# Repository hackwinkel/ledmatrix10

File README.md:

# ledmatrix10
10x10 RGB led display using "dumb" leds and an ESP32 to drive them

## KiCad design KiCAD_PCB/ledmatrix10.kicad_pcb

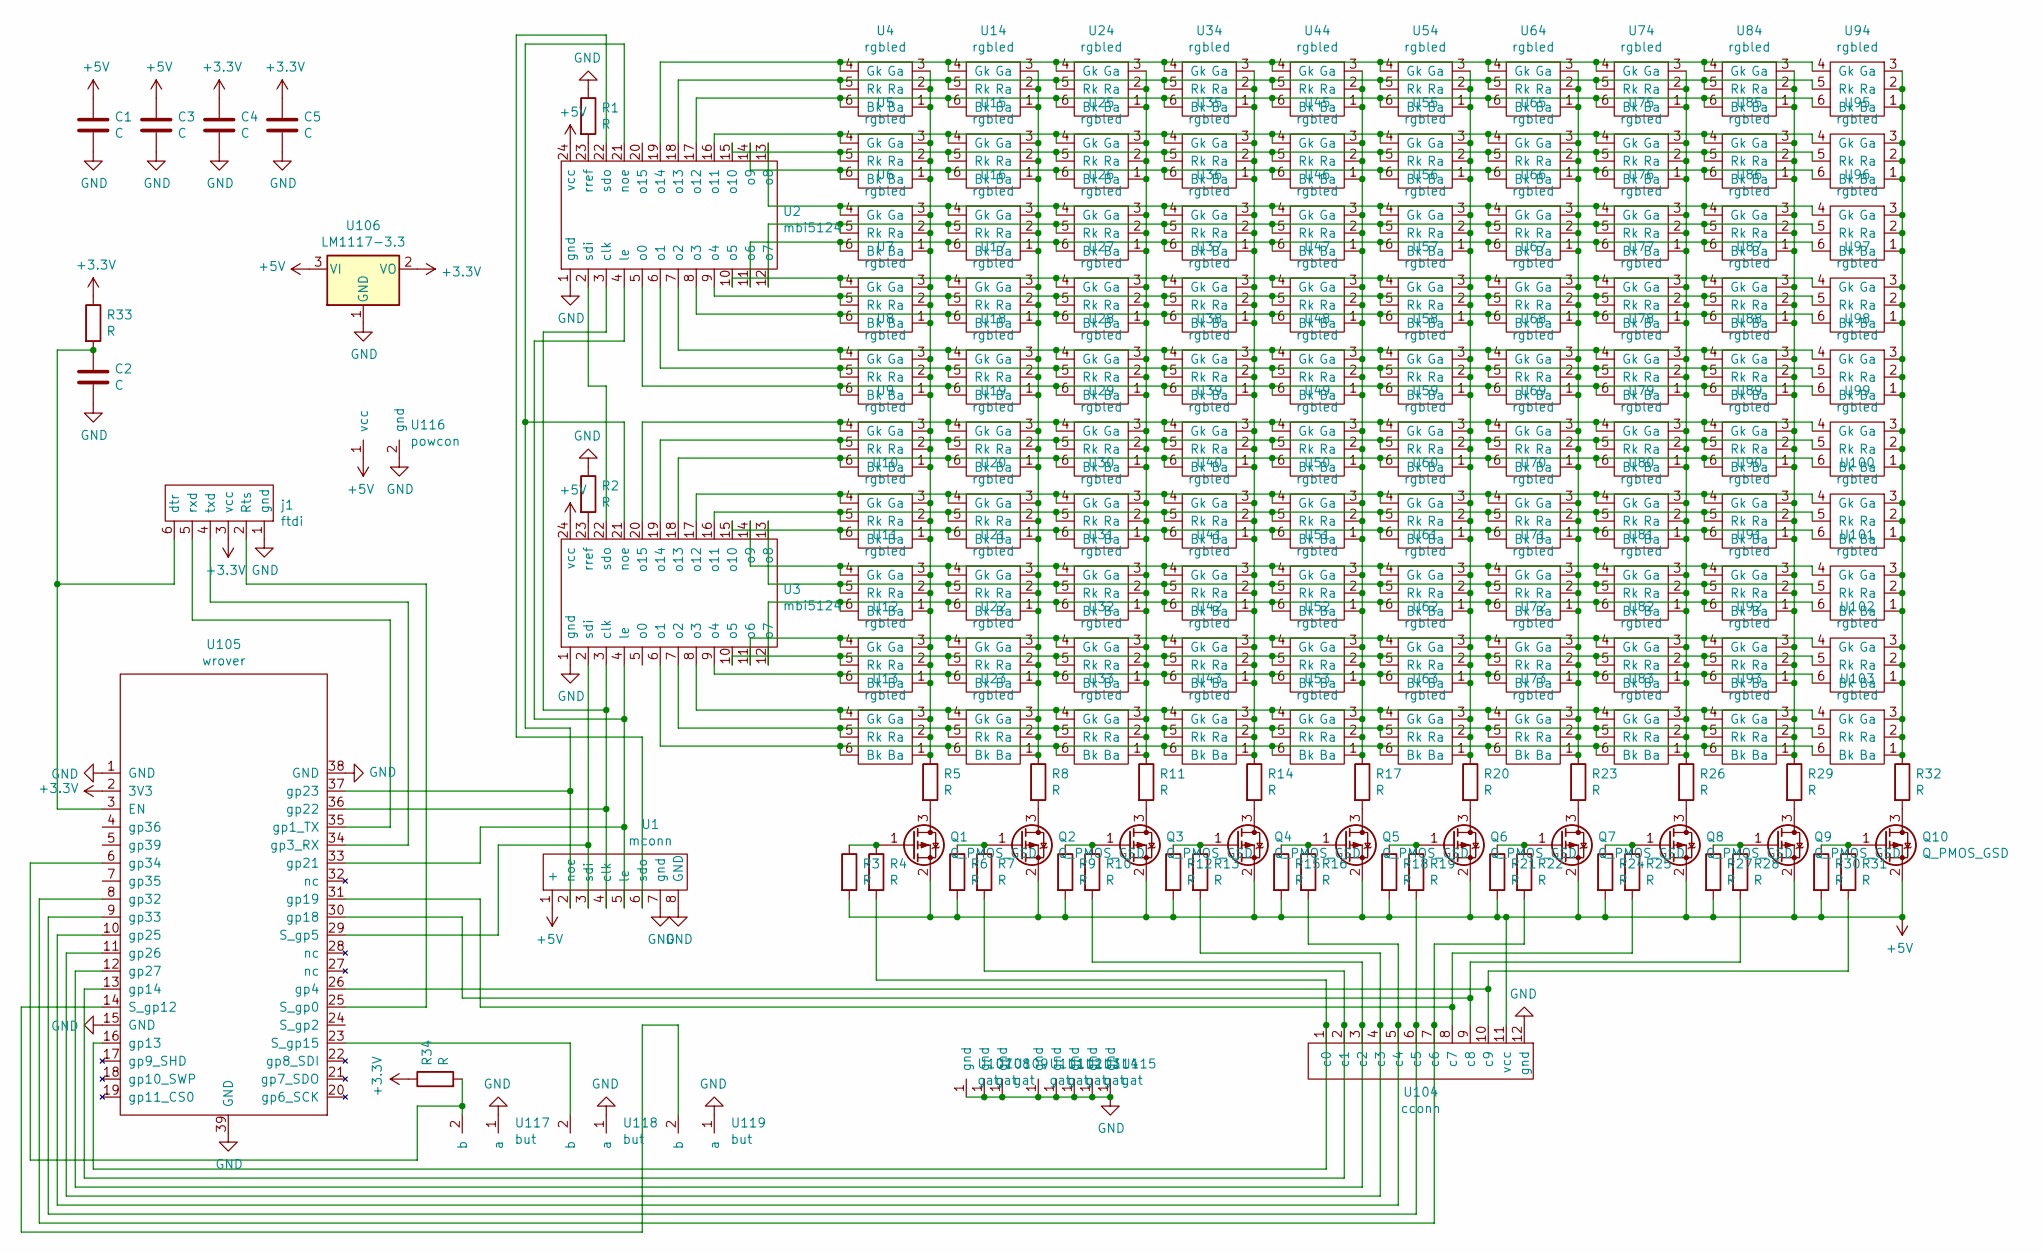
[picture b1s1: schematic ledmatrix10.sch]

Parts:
C1, C2, C3, C4, C5: C; C_0805_2012Metric_Pad1.15x1.40mm_HandSolder
Q1, Q2, Q3, Q4, Q5, Q6, Q7, Q8, Q9, Q10: Q_PMOS_GSD; SOT-23_Handsoldering
R1, R2, R3, R4, R5, R6, R7, R8, R9, R10, R11, R12, R13, R14, R15, R16, R17, R18, R19, R20, R21, R22, R23, R24, R25, R26, R27, R28, R29, R30, R31, R32, R33, R34: R; R_0805_2012Metric_Pad1.15x1.40mm_HandSolder
U1: mconn
U2, U3: mbi5124; SSOP-24_3.9x8.7mm_P0.635mm
U4, U5, U6, U7, U8, U9, U10, U11, U12, U13, U14, U15, U16, U17, U18, U19, U20, U21, U22, U23, U24, U25, U26, U27, U28, U29, U30, U31, U32, U33, U34, U35, U36, U37, U38, U39, U40, U41, U42, U43, U44, U45, U46, U47, U48, U49, U50, U51, U52, U53, U54, U55, U56, U57, U58, U59, U60, U61, U62, U63, U64, U65, U66, U67, U68, U69, U70, U71, U72, U73, U74, U75, U76, U77, U78, U79, U80, U81, U82, U83, U84, U85, U86, U87, U88, U89, U90, U91, U92, U93, U94, U95, U96, U97, U98, U99, U100, U101, U102, U103: rgbled; rgbled2
U104: cconn
U105: wrover
U106: LM1117-3.3; SOT-223-3_TabPin2
U107, U108, U109, U111, U112, U113, U114, U115: gat
U116: powcon
U117, U118, U119: but
j1: ftdi; fconn

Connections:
+3V3: C4.1, C5.1, R33.1, R34.1, U105.2 (3V3), U106.2 (VO), j1.3 (vcc)
+5V: C1.1, C3.1, Q1.2 (S), Q2.2 (S), Q3.2 (S), Q4.2 (S), Q5.2 (S), Q6.2 (S), Q7.2 (S), Q8.2 (S), Q9.2 (S), Q10.2 (S), R3.2, R6.2, R9.2, R12.2, R15.2, R18.2, R21.2, R24.2, R27.2, R30.2, U1.1 (+), U2.24 (vcc), U3.24 (vcc), U104.11 (vcc), U106.3 (VI), U116.1 (vcc)
GND: C1.2, C2.2, C3.2, C4.2, C5.2, R1.1, R2.1, U1.7 (gnd), U1.8 (GND), U2.1 (gnd), U3.1 (gnd), U104.12 (gnd), U105.1 (GND), U105.15 (GND), U105.38 (GND), U105.39 (GND), U106.1 (GND), U107.1, U108.1, U109.1, U111.1, U112.1, U113.1, U114.1, U115.1, U116.2 (gnd), U117.1 (a), U118.1 (a), U119.1 (a), j1.1 (gnd)
unnamed: C2.1, R33.2, U105.3 (EN), j1.6 (dtr)
unnamed: Q1.1 (G), R3.1, R4.1
unnamed: Q1.3 (D), R5.2
unnamed: Q2.1 (G), R6.1, R7.1
unnamed: Q2.3 (D), R8.2
unnamed: Q3.1 (G), R9.1, R10.1
unnamed: Q3.3 (D), R11.2
unnamed: Q4.1 (G), R12.1, R13.1
unnamed: Q4.3 (D), R14.2
unnamed: Q5.1 (G), R15.1, R16.1
unnamed: Q5.3 (D), R17.2
unnamed: Q6.1 (G), R18.1, R19.1
unnamed: Q6.3 (D), R20.2
unnamed: Q7.1 (G), R21.1, R22.1
unnamed: Q7.3 (D), R23.2
unnamed: Q8.1 (G), R24.1, R25.1
unnamed: Q8.3 (D), R26.2
unnamed: Q9.1 (G), R27.1, R28.1
unnamed: Q9.3 (D), R29.2
unnamed: Q10.1 (G), R30.1, R31.1
unnamed: Q10.3 (D), R32.2
unnamed: R1.2, U2.23 (rref)
unnamed: R2.2, U3.23 (rref)
unnamed: R4.2, U104.1 (c0), U105.16 (gp13)
unnamed: R5.1, U4.1 (Ba), U4.2 (Ra), U4.3 (Ga), U5.1 (Ba), U5.2 (Ra), U5.3 (Ga), U6.1 (Ba), U6.2 (Ra), U6.3 (Ga), U7.1 (Ba), U7.2 (Ra), U7.3 (Ga), U8.1 (Ba), U8.2 (Ra), U8.3 (Ga), U9.1 (Ba), U9.2 (Ra), U9.3 (Ga), U10.1 (Ba), U10.2 (Ra), U10.3 (Ga), U11.1 (Ba), U11.2 (Ra), U11.3 (Ga), U12.1 (Ba), U12.2 (Ra), U12.3 (Ga), U13.1 (Ba), U13.2 (Ra), U13.3 (Ga)
unnamed: R7.2, U104.2 (c1), U105.13 (gp14)
unnamed: R8.1, U14.1 (Ba), U14.2 (Ra), U14.3 (Ga), U15.1 (Ba), U15.2 (Ra), U15.3 (Ga), U16.1 (Ba), U16.2 (Ra), U16.3 (Ga), U17.1 (Ba), U17.2 (Ra), U17.3 (Ga), U18.1 (Ba), U18.2 (Ra), U18.3 (Ga), U19.1 (Ba), U19.2 (Ra), U19.3 (Ga), U20.1 (Ba), U20.2 (Ra), U20.3 (Ga), U21.1 (Ba), U21.2 (Ra), U21.3 (Ga), U22.1 (Ba), U22.2 (Ra), U22.3 (Ga), U23.1 (Ba), U23.2 (Ra), U23.3 (Ga)
unnamed: R10.2, U104.3 (c2), U105.12 (gp27)
unnamed: R11.1, U24.1 (Ba), U24.2 (Ra), U24.3 (Ga), U25.1 (Ba), U25.2 (Ra), U25.3 (Ga), U26.1 (Ba), U26.2 (Ra), U26.3 (Ga), U27.1 (Ba), U27.2 (Ra), U27.3 (Ga), U28.1 (Ba), U28.2 (Ra), U28.3 (Ga), U29.1 (Ba), U29.2 (Ra), U29.3 (Ga), U30.1 (Ba), U30.2 (Ra), U30.3 (Ga), U31.1 (Ba), U31.2 (Ra), U31.3 (Ga), U32.1 (Ba), U32.2 (Ra), U32.3 (Ga), U33.1 (Ba), U33.2 (Ra), U33.3 (Ga)
unnamed: R13.2, U104.4 (c3), U105.11 (gp26)
unnamed: R14.1, U34.1 (Ba), U34.2 (Ra), U34.3 (Ga), U35.1 (Ba), U35.2 (Ra), U35.3 (Ga), U36.1 (Ba), U36.2 (Ra), U36.3 (Ga), U37.1 (Ba), U37.2 (Ra), U37.3 (Ga), U38.1 (Ba), U38.2 (Ra), U38.3 (Ga), U39.1 (Ba), U39.2 (Ra), U39.3 (Ga), U40.1 (Ba), U40.2 (Ra), U40.3 (Ga), U41.1 (Ba), U41.2 (Ra), U41.3 (Ga), U42.1 (Ba), U42.2 (Ra), U42.3 (Ga), U43.1 (Ba), U43.2 (Ra), U43.3 (Ga)
unnamed: R16.2, U104.5 (c4), U105.10 (gp25)
unnamed: R17.1, U44.1 (Ba), U44.2 (Ra), U44.3 (Ga), U45.1 (Ba), U45.2 (Ra), U45.3 (Ga), U46.1 (Ba), U46.2 (Ra), U46.3 (Ga), U47.1 (Ba), U47.2 (Ra), U47.3 (Ga), U48.1 (Ba), U48.2 (Ra), U48.3 (Ga), U49.1 (Ba), U49.2 (Ra), U49.3 (Ga), U50.1 (Ba), U50.2 (Ra), U50.3 (Ga), U51.1 (Ba), U51.2 (Ra), U51.3 (Ga), U52.1 (Ba), U52.2 (Ra), U52.3 (Ga), U53.1 (Ba), U53.2 (Ra), U53.3 (Ga)
unnamed: R19.2, U104.6 (c5), U105.9 (gp33)
unnamed: R20.1, U54.1 (Ba), U54.2 (Ra), U54.3 (Ga), U55.1 (Ba), U55.2 (Ra), U55.3 (Ga), U56.1 (Ba), U56.2 (Ra), U56.3 (Ga), U57.1 (Ba), U57.2 (Ra), U57.3 (Ga), U58.1 (Ba), U58.2 (Ra), U58.3 (Ga), U59.1 (Ba), U59.2 (Ra), U59.3 (Ga), U60.1 (Ba), U60.2 (Ra), U60.3 (Ga), U61.1 (Ba), U61.2 (Ra), U61.3 (Ga), U62.1 (Ba), U62.2 (Ra), U62.3 (Ga), U63.1 (Ba), U63.2 (Ra), U63.3 (Ga)
unnamed: R22.2, U104.7 (c6), U105.8 (gp32)
unnamed: R23.1, U64.1 (Ba), U64.2 (Ra), U64.3 (Ga), U65.1 (Ba), U65.2 (Ra), U65.3 (Ga), U66.1 (Ba), U66.2 (Ra), U66.3 (Ga), U67.1 (Ba), U67.2 (Ra), U67.3 (Ga), U68.1 (Ba), U68.2 (Ra), U68.3 (Ga), U69.1 (Ba), U69.2 (Ra), U69.3 (Ga), U70.1 (Ba), U70.2 (Ra), U70.3 (Ga), U71.1 (Ba), U71.2 (Ra), U71.3 (Ga), U72.1 (Ba), U72.2 (Ra), U72.3 (Ga), U73.1 (Ba), U73.2 (Ra), U73.3 (Ga)
unnamed: R25.2, U104.8 (c7), U105.31 (gp19)
unnamed: R26.1, U74.1 (Ba), U74.2 (Ra), U74.3 (Ga), U75.1 (Ba), U75.2 (Ra), U75.3 (Ga), U76.1 (Ba), U76.2 (Ra), U76.3 (Ga), U77.1 (Ba), U77.2 (Ra), U77.3 (Ga), U78.1 (Ba), U78.2 (Ra), U78.3 (Ga), U79.1 (Ba), U79.2 (Ra), U79.3 (Ga), U80.1 (Ba), U80.2 (Ra), U80.3 (Ga), U81.1 (Ba), U81.2 (Ra), U81.3 (Ga), U82.1 (Ba), U82.2 (Ra), U82.3 (Ga), U83.1 (Ba), U83.2 (Ra), U83.3 (Ga)
unnamed: R28.2, U104.9 (c8), U105.30 (gp18)
unnamed: R29.1, U84.1 (Ba), U84.2 (Ra), U84.3 (Ga), U85.1 (Ba), U85.2 (Ra), U85.3 (Ga), U86.1 (Ba), U86.2 (Ra), U86.3 (Ga), U87.1 (Ba), U87.2 (Ra), U87.3 (Ga), U88.1 (Ba), U88.2 (Ra), U88.3 (Ga), U89.1 (Ba), U89.2 (Ra), U89.3 (Ga), U90.1 (Ba), U90.2 (Ra), U90.3 (Ga), U91.1 (Ba), U91.2 (Ra), U91.3 (Ga), U92.1 (Ba), U92.2 (Ra), U92.3 (Ga), U93.1 (Ba), U93.2 (Ra), U93.3 (Ga)
unnamed: R31.2, U104.10 (c9), U105.26 (gp4)
unnamed: R32.1, U94.1 (Ba), U94.2 (Ra), U94.3 (Ga), U95.1 (Ba), U95.2 (Ra), U95.3 (Ga), U96.1 (Ba), U96.2 (Ra), U96.3 (Ga), U97.1 (Ba), U97.2 (Ra), U97.3 (Ga), U98.1 (Ba), U98.2 (Ra), U98.3 (Ga), U99.1 (Ba), U99.2 (Ra), U99.3 (Ga), U100.1 (Ba), U100.2 (Ra), U100.3 (Ga), U101.1 (Ba), U101.2 (Ra), U101.3 (Ga), U102.1 (Ba), U102.2 (Ra), U102.3 (Ga), U103.1 (Ba), U103.2 (Ra), U103.3 (Ga)
unnamed: R34.2, U105.6 (gp34), U117.2 (b)
unnamed: U1.2 (noe), U2.21 (noe), U3.21 (noe), U105.37 (gp23)
unnamed: U1.3 (sdi), U3.2 (sdi), U105.29 (S_gp5)
unnamed: U1.4 (clk), U2.3 (clk), U3.3 (clk), U105.36 (gp22)
unnamed: U1.5 (le), U2.4 (le), U3.4 (le), U105.33 (gp21)
unnamed: U1.6 (sdo), U2.22 (sdo)
unnamed: U2.2 (sdi), U3.22 (sdo)
unnamed: U3.17 (o12), U10.4 (Gk), U20.4 (Gk), U30.4 (Gk), U40.4 (Gk), U50.4 (Gk), U60.4 (Gk), U70.4 (Gk), U80.4 (Gk), U90.4 (Gk), U100.4 (Gk)
unnamed: U3.16 (o11), U10.5 (Rk), U20.5 (Rk), U30.5 (Rk), U40.5 (Rk), U50.5 (Rk), U60.5 (Rk), U70.5 (Rk), U80.5 (Rk), U90.5 (Rk), U100.5 (Rk)
unnamed: U3.15 (o10), U10.6 (Bk), U20.6 (Bk), U30.6 (Bk), U40.6 (Bk), U50.6 (Bk), U60.6 (Bk), U70.6 (Bk), U80.6 (Bk), U90.6 (Bk), U100.6 (Bk)
unnamed: U2.19 (o14), U4.4 (Gk), U14.4 (Gk), U24.4 (Gk), U34.4 (Gk), U44.4 (Gk), U54.4 (Gk), U64.4 (Gk), U74.4 (Gk), U84.4 (Gk), U94.4 (Gk)
unnamed: U2.18 (o13), U4.5 (Rk), U14.5 (Rk), U24.5 (Rk), U34.5 (Rk), U44.5 (Rk), U54.5 (Rk), U64.5 (Rk), U74.5 (Rk), U84.5 (Rk), U94.5 (Rk)
unnamed: U2.17 (o12), U4.6 (Bk), U14.6 (Bk), U24.6 (Bk), U34.6 (Bk), U44.6 (Bk), U54.6 (Bk), U64.6 (Bk), U74.6 (Bk), U84.6 (Bk), U94.6 (Bk)
unnamed: U2.16 (o11), U5.4 (Gk), U15.4 (Gk), U25.4 (Gk), U35.4 (Gk), U45.4 (Gk), U55.4 (Gk), U65.4 (Gk), U75.4 (Gk), U85.4 (Gk), U95.4 (Gk)
unnamed: U2.15 (o10), U5.5 (Rk), U15.5 (Rk), U25.5 (Rk), U35.5 (Rk), U45.5 (Rk), U55.5 (Rk), U65.5 (Rk), U75.5 (Rk), U85.5 (Rk), U95.5 (Rk)
unnamed: U2.14 (o9), U5.6 (Bk), U15.6 (Bk), U25.6 (Bk), U35.6 (Bk), U45.6 (Bk), U55.6 (Bk), U65.6 (Bk), U75.6 (Bk), U85.6 (Bk), U95.6 (Bk)
unnamed: U2.13 (o8), U6.4 (Gk), U16.4 (Gk), U26.4 (Gk), U36.4 (Gk), U46.4 (Gk), U56.4 (Gk), U66.4 (Gk), U76.4 (Gk), U86.4 (Gk), U96.4 (Gk)
unnamed: U2.12 (o7), U6.5 (Rk), U16.5 (Rk), U26.5 (Rk), U36.5 (Rk), U46.5 (Rk), U56.5 (Rk), U66.5 (Rk), U76.5 (Rk), U86.5 (Rk), U96.5 (Rk)
unnamed: U2.11 (o6), U6.6 (Bk), U16.6 (Bk), U26.6 (Bk), U36.6 (Bk), U46.6 (Bk), U56.6 (Bk), U66.6 (Bk), U76.6 (Bk), U86.6 (Bk), U96.6 (Bk)
unnamed: U2.10 (o5), U7.4 (Gk), U17.4 (Gk), U27.4 (Gk), U37.4 (Gk), U47.4 (Gk), U57.4 (Gk), U67.4 (Gk), U77.4 (Gk), U87.4 (Gk), U97.4 (Gk)
unnamed: U2.9 (o4), U7.5 (Rk), U17.5 (Rk), U27.5 (Rk), U37.5 (Rk), U47.5 (Rk), U57.5 (Rk), U67.5 (Rk), U77.5 (Rk), U87.5 (Rk), U97.5 (Rk)
unnamed: U2.8 (o3), U7.6 (Bk), U17.6 (Bk), U27.6 (Bk), U37.6 (Bk), U47.6 (Bk), U57.6 (Bk), U67.6 (Bk), U77.6 (Bk), U87.6 (Bk), U97.6 (Bk)
unnamed: U2.7 (o2), U8.4 (Gk), U18.4 (Gk), U28.4 (Gk), U38.4 (Gk), U48.4 (Gk), U58.4 (Gk), U68.4 (Gk), U78.4 (Gk), U88.4 (Gk), U98.4 (Gk)
unnamed: U2.6 (o1), U8.5 (Rk), U18.5 (Rk), U28.5 (Rk), U38.5 (Rk), U48.5 (Rk), U58.5 (Rk), U68.5 (Rk), U78.5 (Rk), U88.5 (Rk), U98.5 (Rk)
unnamed: U2.5 (o0), U8.6 (Bk), U18.6 (Bk), U28.6 (Bk), U38.6 (Bk), U48.6 (Bk), U58.6 (Bk), U68.6 (Bk), U78.6 (Bk), U88.6 (Bk), U98.6 (Bk)
unnamed: U3.20 (o15), U9.4 (Gk), U19.4 (Gk), U29.4 (Gk), U39.4 (Gk), U49.4 (Gk), U59.4 (Gk), U69.4 (Gk), U79.4 (Gk), U89.4 (Gk), U99.4 (Gk)
unnamed: U3.19 (o14), U9.5 (Rk), U19.5 (Rk), U29.5 (Rk), U39.5 (Rk), U49.5 (Rk), U59.5 (Rk), U69.5 (Rk), U79.5 (Rk), U89.5 (Rk), U99.5 (Rk)
unnamed: U3.18 (o13), U9.6 (Bk), U19.6 (Bk), U29.6 (Bk), U39.6 (Bk), U49.6 (Bk), U59.6 (Bk), U69.6 (Bk), U79.6 (Bk), U89.6 (Bk), U99.6 (Bk)
unnamed: U3.14 (o9), U11.4 (Gk), U21.4 (Gk), U31.4 (Gk), U41.4 (Gk), U51.4 (Gk), U61.4 (Gk), U71.4 (Gk), U81.4 (Gk), U91.4 (Gk), U101.4 (Gk)
unnamed: U3.13 (o8), U11.5 (Rk), U21.5 (Rk), U31.5 (Rk), U41.5 (Rk), U51.5 (Rk), U61.5 (Rk), U71.5 (Rk), U81.5 (Rk), U91.5 (Rk), U101.5 (Rk)
unnamed: U3.12 (o7), U11.6 (Bk), U21.6 (Bk), U31.6 (Bk), U41.6 (Bk), U51.6 (Bk), U61.6 (Bk), U71.6 (Bk), U81.6 (Bk), U91.6 (Bk), U101.6 (Bk)
unnamed: U3.11 (o6), U12.4 (Gk), U22.4 (Gk), U32.4 (Gk), U42.4 (Gk), U52.4 (Gk), U62.4 (Gk), U72.4 (Gk), U82.4 (Gk), U92.4 (Gk), U102.4 (Gk)
unnamed: U3.10 (o5), U12.5 (Rk), U22.5 (Rk), U32.5 (Rk), U42.5 (Rk), U52.5 (Rk), U62.5 (Rk), U72.5 (Rk), U82.5 (Rk), U92.5 (Rk), U102.5 (Rk)
unnamed: U3.9 (o4), U12.6 (Bk), U22.6 (Bk), U32.6 (Bk), U42.6 (Bk), U52.6 (Bk), U62.6 (Bk), U72.6 (Bk), U82.6 (Bk), U92.6 (Bk), U102.6 (Bk)
unnamed: U3.8 (o3), U13.4 (Gk), U23.4 (Gk), U33.4 (Gk), U43.4 (Gk), U53.4 (Gk), U63.4 (Gk), U73.4 (Gk), U83.4 (Gk), U93.4 (Gk), U103.4 (Gk)
unnamed: U3.7 (o2), U13.5 (Rk), U23.5 (Rk), U33.5 (Rk), U43.5 (Rk), U53.5 (Rk), U63.5 (Rk), U73.5 (Rk), U83.5 (Rk), U93.5 (Rk), U103.5 (Rk)
unnamed: U3.6 (o1), U13.6 (Bk), U23.6 (Bk), U33.6 (Bk), U43.6 (Bk), U53.6 (Bk), U63.6 (Bk), U73.6 (Bk), U83.6 (Bk), U93.6 (Bk), U103.6 (Bk)
unnamed: U105.14 (S_gp12), U119.2 (b)
unnamed: U105.23 (S_gp15), U118.2 (b)
unnamed: U105.25 (S_gp0), j1.2 (Rts)
unnamed: U105.34 (gp3_RX), j1.4 (txd)
unnamed: U105.35 (gp1_TX), j1.5 (rxd)

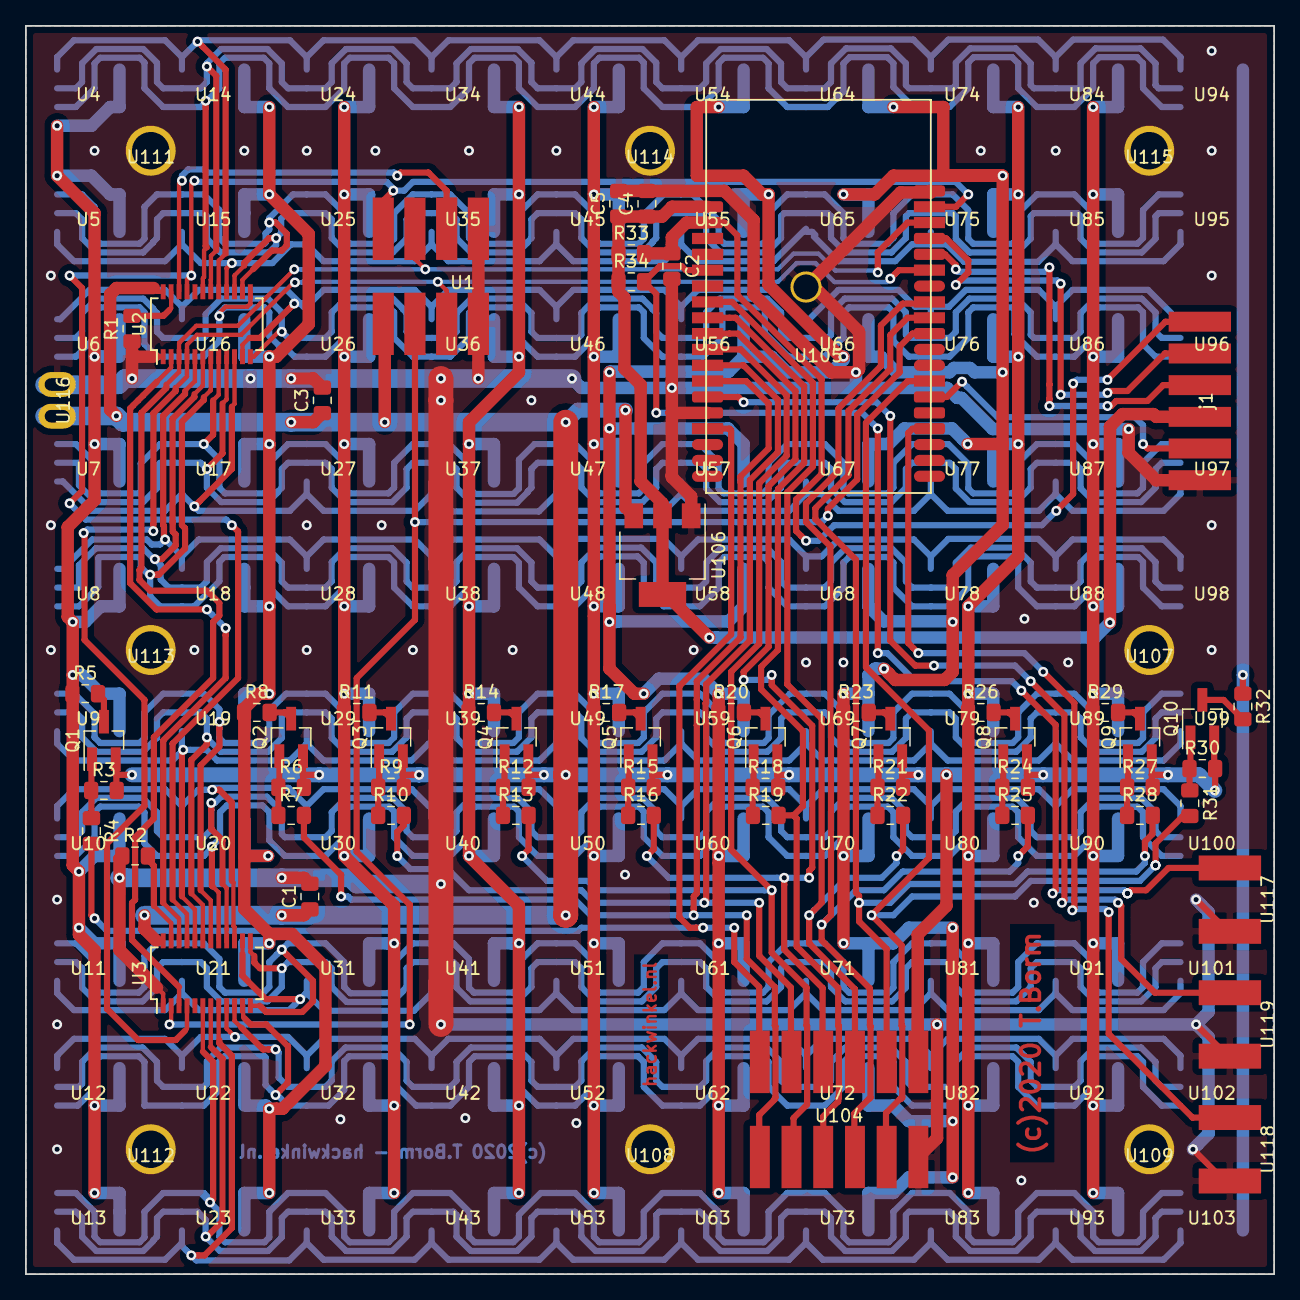
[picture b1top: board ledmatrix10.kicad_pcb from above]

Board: 2 copper layers, 100.0 x 100.0 mm, 168 parts (0 on the bottom side), 88 nets.

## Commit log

2020-09-22 initial commit of a 10x10 dumb RGB led driver board using MBI5124's and an ESP32 wrover to control them

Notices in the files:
KiCAD_PCB/ledmatrix10.kicad_pcb:
(c)2020 T.Borm - hackwinkel.nl
(c)2020 T.Borm
